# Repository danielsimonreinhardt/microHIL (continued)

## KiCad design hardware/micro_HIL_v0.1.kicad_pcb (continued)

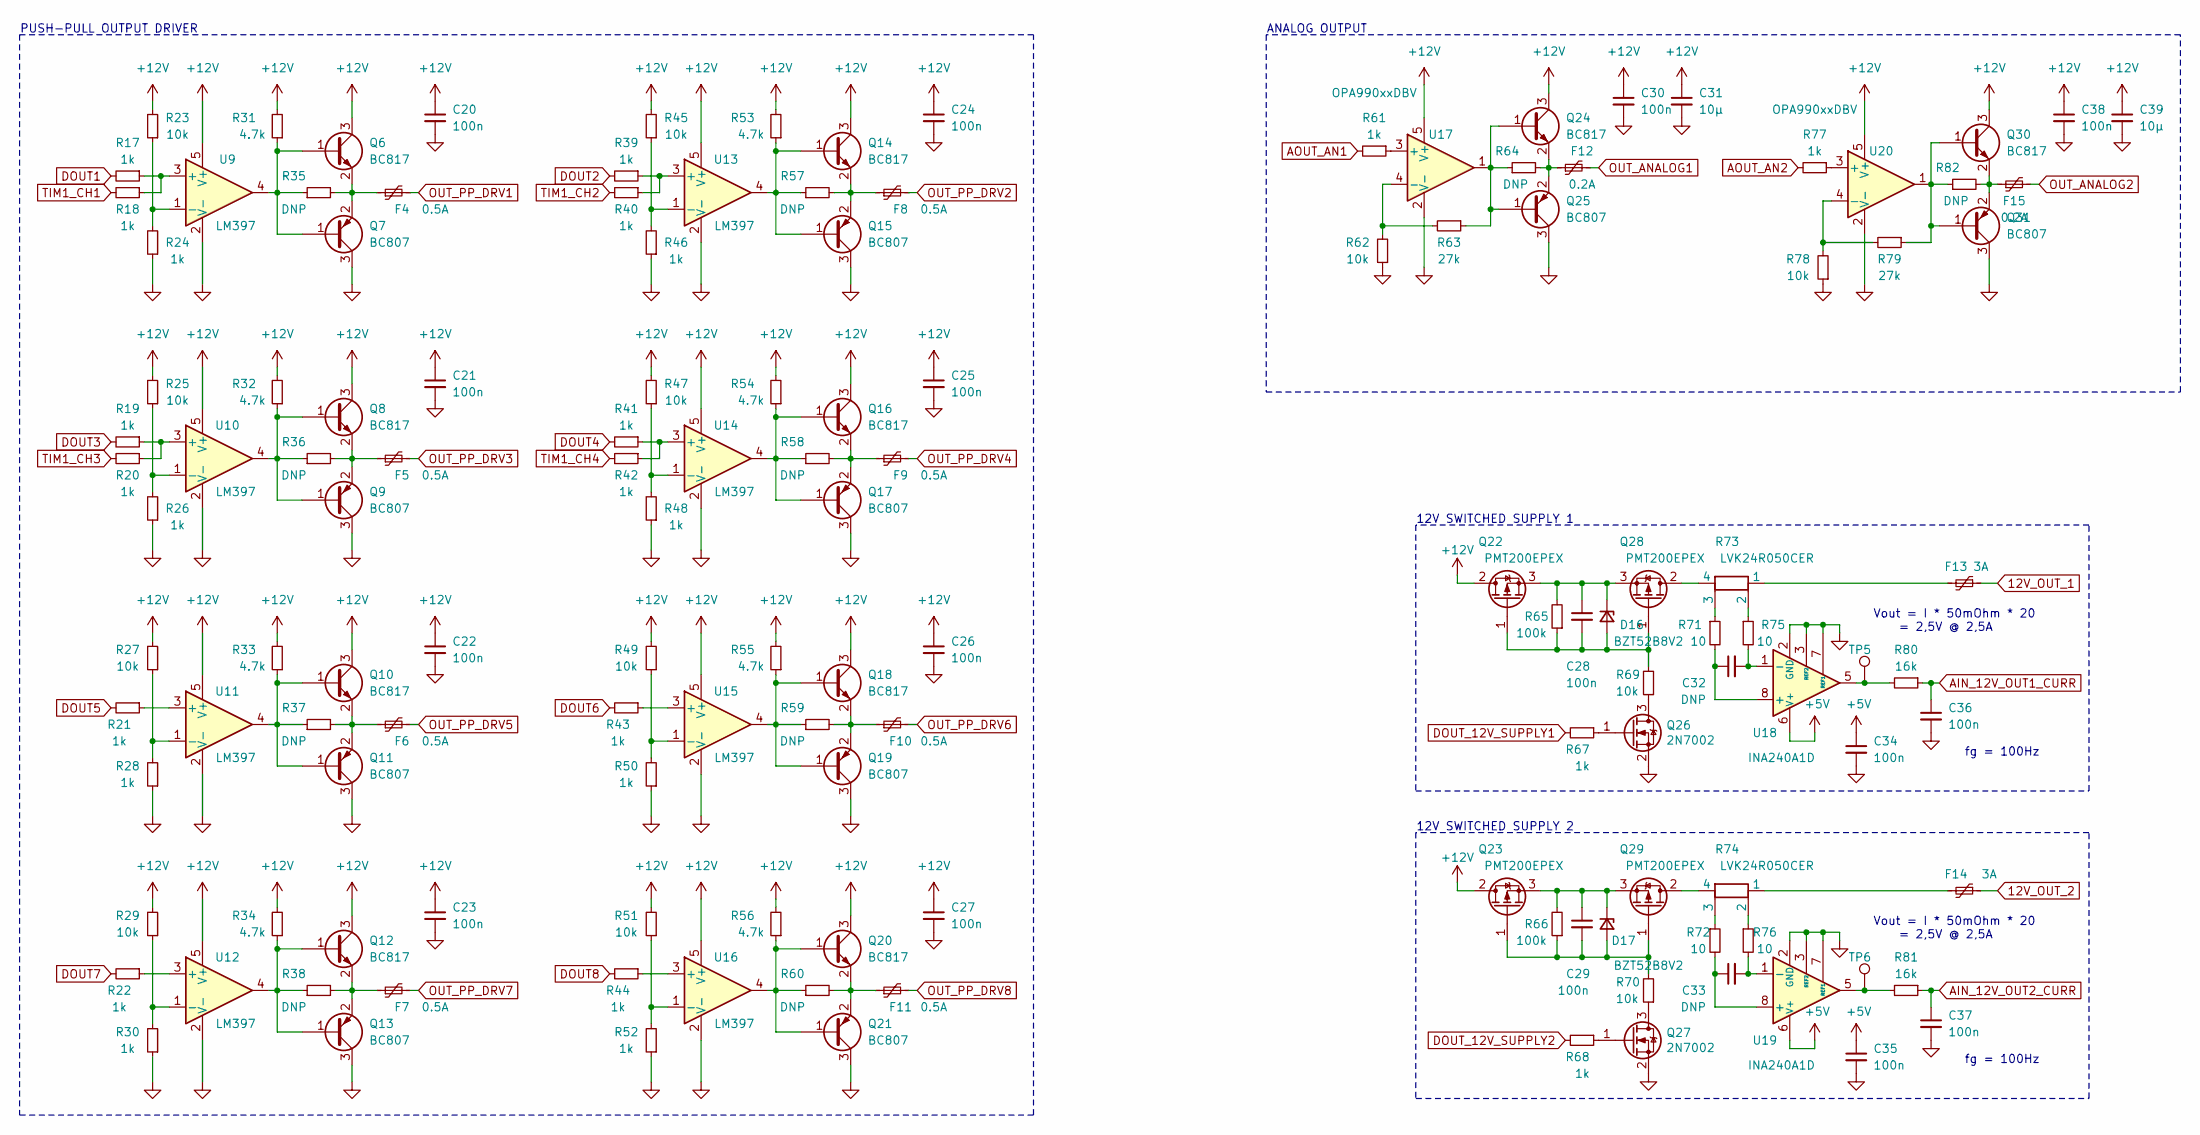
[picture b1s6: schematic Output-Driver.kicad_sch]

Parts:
C20, C21, C22, C23, C24, C25, C26, C27, C28, C29, C30, C34, C35, C36, C37, C38: 100n; C_0603_1608Metric
C31, C39: 10µ; C_0805_2012Metric
C32, C33: DNP; C_0603_1608Metric
D16, D17: BZT52B8V2; D_SOD-123
F4, F5, F6, F7, F8, F9, F10, F11: 0.5A; Fuse_1210_3225Metric
F12, F15: 0.2A; Fuse_1210_3225Metric
F13, F14: 3A; Fuse_1812_4532Metric
Q6, Q8, Q10, Q12, Q14, Q16, Q18, Q20, Q24, Q30: BC817; SOT-23
Q7, Q9, Q11, Q13, Q15, Q17, Q19, Q21, Q25, Q31: BC807; SOT-23
Q22, Q23, Q28, Q29: PMT200EPEX; SOT-223-3_TabPin2
Q26, Q27: 2N7002; SOT-23
R17, R18, R19, R20, R21, R22, R24, R26, R28, R30, R39, R40, R41, R42, R43, R44, R46, R48, R50, R52, R61, R67, R68, R77: 1k; R_0603_1608Metric
R23, R25, R27, R29, R45, R47, R49, R51, R62, R69, R70, R78: 10k; R_0603_1608Metric
R31, R32, R33, R34, R53, R54, R55, R56: 4.7k; R_0603_1608Metric
R35, R36, R37, R38, R57, R58, R59, R60, R64, R82: DNP; R_0603_1608Metric
R63, R79: 27k; R_0603_1608Metric
R65, R66: 100k; R_0603_1608Metric
R71, R72, R75, R76: 10; R_0603_1608Metric
R73, R74: LVK24R050CER; R_Shunt_Ohmite_LVK24
R80, R81: 16k; R_0603_1608Metric
TP5, TP6: TestPoint; TestPoint_Pad_D1.0mm
U9, U10, U11, U12, U13, U14, U15, U16: LM397; SOT-23-5
U17, U20: OPA990xxDBV; SOT-23-5
U18, U19: INA240A1D; SOIC-8_3.9x4.9mm_P1.27mm

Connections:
12V_OUT_1: F13.1; also elsewhere on the board
12V_OUT_2: F14.1; also elsewhere on the board
+5V: C34.1, C35.1, U18.6 (V+), U19.6 (V+); also elsewhere on the board
+12V: C20.1, C21.1, C22.1, C23.1, C24.1, C25.1, C26.1, C27.1, C30.1, C31.1, C38.1, C39.1, Q6.3 (C), Q8.3 (C), Q10.3 (C), Q12.3 (C), Q14.3 (C), Q16.3 (C), Q18.3 (C), Q20.3 (C), Q22.2 (D), Q23.2 (D), Q24.3 (C), Q30.3 (C), R23.2, R25.2, R27.2, R29.2, R31.2, R32.2, R33.2, R34.2, R45.2, R47.2, R49.2, R51.2, R53.2, R54.2, R55.2, R56.2, U9.5 (V+), U10.5 (V+), U11.5 (V+), U12.5 (V+), U13.5 (V+), U14.5 (V+), U15.5 (V+), U16.5 (V+), U17.5 (V+), U20.5 (V+); also elsewhere on the board
AIN_12V_OUT1_CURR: C36.1, R80.1; also elsewhere on the board
AIN_12V_OUT2_CURR: C37.1, R81.1; also elsewhere on the board
AOUT_AN1: R61.2; also elsewhere on the board
AOUT_AN2: R77.2; also elsewhere on the board
DOUT1: R17.2; also elsewhere on the board
DOUT2: R39.2; also elsewhere on the board
DOUT3: R19.2; also elsewhere on the board
DOUT4: R41.2; also elsewhere on the board
DOUT5: R21.2; also elsewhere on the board
DOUT6: R43.2; also elsewhere on the board
DOUT7: R22.2; also elsewhere on the board
DOUT8: R44.2; also elsewhere on the board
DOUT_12V_SUPPLY1: R67.2; also elsewhere on the board
DOUT_12V_SUPPLY2: R68.2; also elsewhere on the board
GND: C20.2, C21.2, C22.2, C23.2, C24.2, C25.2, C26.2, C27.2, C30.2, C31.2, C34.2, C35.2, C36.2, C37.2, C38.2, C39.2, Q7.3 (C), Q9.3 (C), Q11.3 (C), Q13.3 (C), Q15.3 (C), Q17.3 (C), Q19.3 (C), Q21.3 (C), Q25.3 (C), Q26.2 (S), Q27.2 (S), Q31.3 (C), R24.1, R26.1, R28.1, R30.1, R46.1, R48.1, R50.1, R52.1, R62.1, R78.1, U9.2 (V-), U10.2 (V-), U11.2 (V-), U12.2 (V-), U13.2 (V-), U14.2 (V-), U15.2 (V-), U16.2 (V-), U17.2 (V-), U18.2 (GND), U18.3 (REF2), U18.4 (GND), U18.7 (REF1), U19.2 (GND), U19.3 (REF2), U19.4 (GND), U19.7 (REF1), U20.2 (V-); also elsewhere on the board
unnamed: C28.1, D16.1 (K), Q22.3 (S), Q28.3 (S), R65.2
unnamed: C28.2, D16.2 (A), Q22.1 (G), Q28.1 (G), R65.1, R69.2
unnamed: C29.1, D17.1 (K), Q23.3 (S), Q29.3 (S), R66.2
unnamed: C29.2, D17.2 (A), Q23.1 (G), Q29.1 (G), R66.1, R70.2
unnamed: C32.1, R71.2, U18.8 (+)
unnamed: C32.2, R75.2, U18.1 (-)
unnamed: C33.1, R72.2, U19.8 (+)
unnamed: C33.2, R76.2, U19.1 (-)
unnamed: F4.1, Q6.2 (E), Q7.2 (E), R35.2
unnamed: F5.1, Q8.2 (E), Q9.2 (E), R36.2
unnamed: F6.1, Q10.2 (E), Q11.2 (E), R37.2
unnamed: F7.1, Q12.2 (E), Q13.2 (E), R38.2
unnamed: F8.1, Q14.2 (E), Q15.2 (E), R57.2
unnamed: F9.1, Q16.2 (E), Q17.2 (E), R58.2
unnamed: F10.1, Q18.2 (E), Q19.2 (E), R59.2
unnamed: F11.1, Q20.2 (E), Q21.2 (E), R60.2
unnamed: F12.1, Q24.2 (E), Q25.2 (E), R64.2
unnamed: F13.2, R73.1
unnamed: F14.2, R74.1
unnamed: F15.1, Q30.2 (E), Q31.2 (E), R82.2
unnamed: Q6.1 (B), Q7.1 (B), R31.1, R35.1, U9.4
unnamed: Q8.1 (B), Q9.1 (B), R32.1, R36.1, U10.4
unnamed: Q10.1 (B), Q11.1 (B), R33.1, R37.1, U11.4
unnamed: Q12.1 (B), Q13.1 (B), R34.1, R38.1, U12.4
unnamed: Q14.1 (B), Q15.1 (B), R53.1, R57.1, U13.4
unnamed: Q16.1 (B), Q17.1 (B), R54.1, R58.1, U14.4
unnamed: Q18.1 (B), Q19.1 (B), R55.1, R59.1, U15.4
unnamed: Q20.1 (B), Q21.1 (B), R56.1, R60.1, U16.4
unnamed: Q24.1 (B), Q25.1 (B), R63.1, R64.1, U17.1
unnamed: Q26.1 (G), R67.1
unnamed: Q26.3 (D), R69.1
unnamed: Q27.1 (G), R68.1
unnamed: Q27.3 (D), R70.1
unnamed: Q28.2 (D), R73.4
unnamed: Q29.2 (D), R74.4
unnamed: Q30.1 (B), Q31.1 (B), R79.1, R82.1, U20.1
unnamed: R17.1, R18.1, U9.3 (+)
unnamed: R19.1, R20.1, U10.3 (+)
unnamed: R21.1, U11.3 (+)
unnamed: R22.1, U12.3 (+)
unnamed: R23.1, R24.2, U9.1 (-)
unnamed: R25.1, R26.2, U10.1 (-)
unnamed: R27.1, R28.2, U11.1 (-)
unnamed: R29.1, R30.2, U12.1 (-)
unnamed: R39.1, R40.1, U13.3 (+)
unnamed: R41.1, R42.1, U14.3 (+)
unnamed: R43.1, U15.3 (+)
unnamed: R44.1, U16.3 (+)
unnamed: R45.1, R46.2, U13.1 (-)
unnamed: R47.1, R48.2, U14.1 (-)
unnamed: R49.1, R50.2, U15.1 (-)
unnamed: R51.1, R52.2, U16.1 (-)
unnamed: R61.1, U17.3 (+)
unnamed: R62.2, R63.2, U17.4 (-)
unnamed: R71.1, R73.3
unnamed: R72.1, R74.3
unnamed: R73.2, R75.1
unnamed: R74.2, R76.1
unnamed: R77.1, U20.3 (+)
unnamed: R78.2, R79.2, U20.4 (-)
unnamed: R80.2, TP5.1, U18.5
unnamed: R81.2, TP6.1, U19.5
OUT_ANALOG1: F12.2; also elsewhere on the board
OUT_ANALOG2: F15.2; also elsewhere on the board
OUT_PP_DRV1: F4.2; also elsewhere on the board
OUT_PP_DRV2: F8.2; also elsewhere on the board
OUT_PP_DRV3: F5.2; also elsewhere on the board
OUT_PP_DRV4: F9.2; also elsewhere on the board
OUT_PP_DRV5: F6.2; also elsewhere on the board
OUT_PP_DRV6: F10.2; also elsewhere on the board
OUT_PP_DRV7: F7.2; also elsewhere on the board
OUT_PP_DRV8: F11.2; also elsewhere on the board
TIM1_CH1: R18.2; also elsewhere on the board
TIM1_CH2: R40.2; also elsewhere on the board
TIM1_CH3: R20.2; also elsewhere on the board
TIM1_CH4: R42.2; also elsewhere on the board

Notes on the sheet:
Vout = I * 50mOhm * 20 = 2,5V @ 2,5A
12V SWITCHED SUPPLY 2
fg = 100Hz
ANALOG OUTPUT
12V SWITCHED SUPPLY 1
PUSH-PULL OUTPUT DRIVER

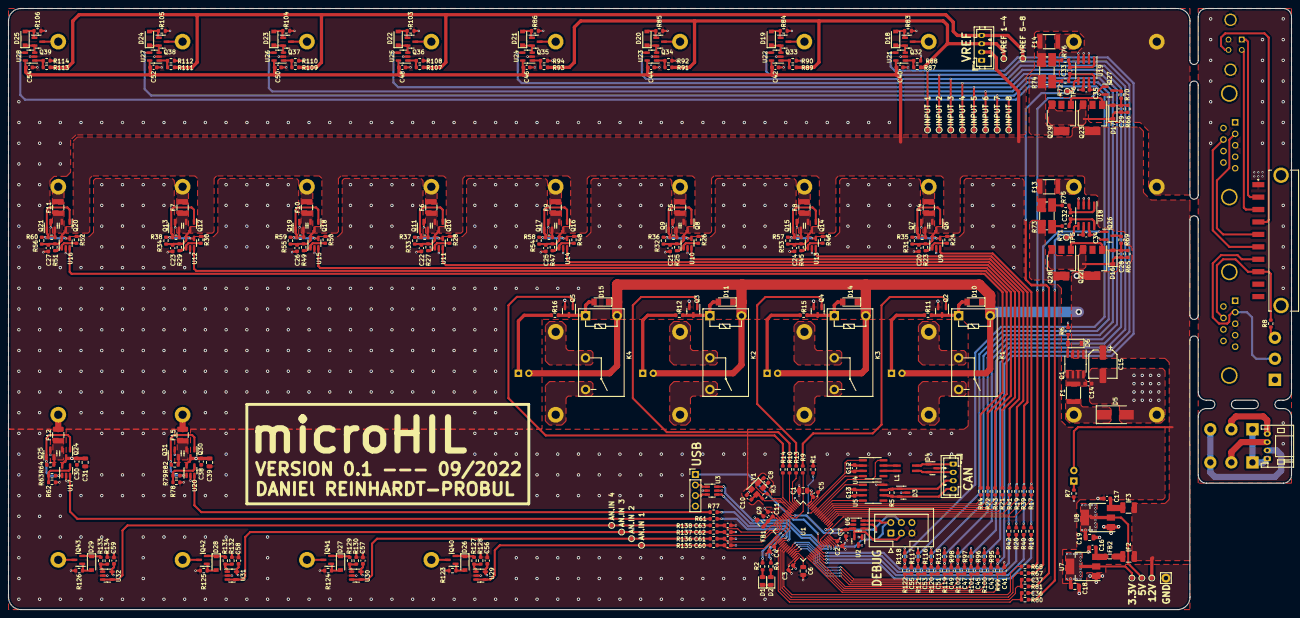
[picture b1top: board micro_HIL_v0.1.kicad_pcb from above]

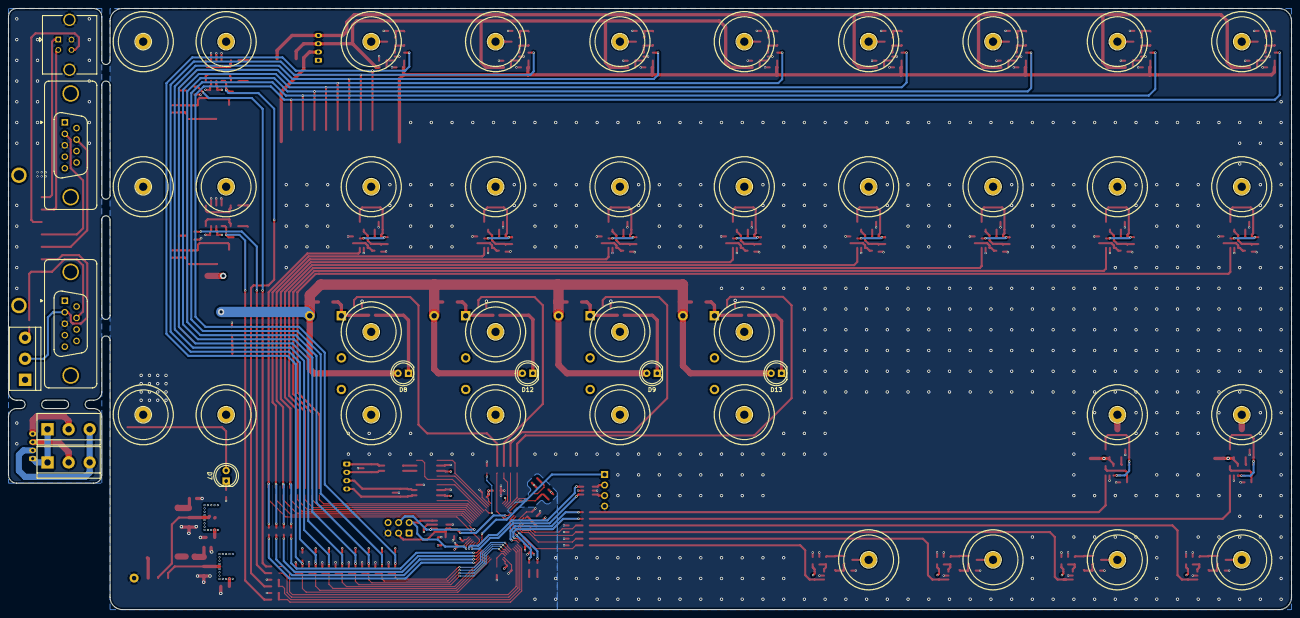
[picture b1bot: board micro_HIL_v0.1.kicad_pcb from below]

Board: 4 copper layers, 309.5 x 145.0 mm, 396 parts (47 on the bottom side), 242 nets.

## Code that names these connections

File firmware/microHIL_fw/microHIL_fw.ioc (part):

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Mcu.Name=STM32F446R(C-E)Tx
Mcu.Package=LQFP64
Mcu.UserName=STM32F446RETx
PA0-WKUP.GPIOParameters=GPIO_Label
PA0-WKUP.GPIO_Label=AIN_AN2
PA0-WKUP.Signal=ADCx_IN0
PA1.GPIOParameters=GPIO_Label
PA1.GPIO_Label=AIN_AN3
PA1.Signal=ADCx_IN1
PA10.GPIOParameters=GPIO_Label
PA10.GPIO_Label=DOUT_OUT1
PA10.Signal=GPIO_Output
PA11.Mode=Device_Only
PA11.Signal=USB_OTG_FS_DM
PA12.Mode=Device_Only
PA12.Signal=USB_OTG_FS_DP
PA13.Mode=Serial_Wire
PA13.Signal=SYS_JTMS-SWDIO
PA14.Mode=Serial_Wire
PA14.Signal=SYS_JTCK-SWCLK
PA15.GPIOParameters=GPIO_Label
PA15.GPIO_Label=DOUT_OUT2
PA15.Signal=GPIO_Output
PA2.GPIOParameters=GPIO_Label
PA2.GPIO_Label=AIN_AN4
PA2.Signal=ADCx_IN2
PA3.GPIOParameters=GPIO_Label
PA3.GPIO_Label=AIN_AN1
PA3.Signal=ADCx_IN3
PA4.GPIOParameters=GPIO_Label
PA4.GPIO_Label=AOUT_AN2
PA4.Signal=COMP_DAC1_group
PA5.GPIOParameters=GPIO_Label
PA5.GPIO_Label=AOUT_AN1
PA5.Signal=COMP_DAC2_group
PA6.GPIOParameters=GPIO_Label
PA6.GPIO_Label=AIN_12VOUT1_CURRSENSE
PA6.Signal=ADCx_IN6
PA7.GPIOParameters=GPIO_Label
PA7.GPIO_Label=AIN_12VOUT2_CURRSENSE
PA7.Signal=ADCx_IN7
PB0.GPIOParameters=GPIO_Label
PB0.GPIO_Label=DIN_IN8
PB0.Signal=GPIO_Input
PB1.GPIOParameters=GPIO_Label
PB1.GPIO_Label=DIN_IN7
PB1.Signal=GPIO_Input
PB10.GPIOParameters=GPIO_Label
PB10.GPIO_Label=DIN_IN5
PB10.Signal=GPIO_Input
PB12.GPIOParameters=GPIO_Label
PB12.GPIO_Label=DIN_IN1
PB12.Signal=GPIO_Input
PB13.GPIOParameters=GPIO_Label
PB13.GPIO_Label=DIN_IN2
PB13.Signal=GPIO_Input
PB14.GPIOParameters=GPIO_Label
PB14.GPIO_Label=DIN_IN3
PB14.Signal=GPIO_Input
PB15.GPIOParameters=GPIO_Label
PB15.GPIO_Label=DIN_IN4
PB15.Signal=GPIO_Input
PB2.GPIOParameters=GPIO_Label
PB2.GPIO_Label=DIN_IN6
PB2.Signal=GPIO_Input
PB3.GPIOParameters=GPIO_Label
PB3.GPIO_Label=DOUT_OUT7
PB3.Signal=GPIO_Output
PB4.GPIOParameters=GPIO_Label
PB4.GPIO_Label=DOUT_OUT8
PB4.Signal=GPIO_Output
PB5.Mode=CAN_Activate
PB5.Signal=CAN2_RX
PB6.Mode=CAN_Activate
PB6.Signal=CAN2_TX
PB7.GPIOParameters=GPIO_Label
PB7.GPIO_Label=CAN1_SILENT
PB7.Signal=GPIO_Output
PB8.Mode=CAN_Activate
PB8.Signal=CAN1_RX
PB9.Mode=CAN_Activate
PB9.Signal=CAN1_TX
PC0.GPIOParameters=GPIO_Label
PC0.GPIO_Label=DOUT_RELAY1
PC0.Signal=GPIO_Output
PC1.GPIOParameters=GPIO_Label
PC1.GPIO_Label=DEBUG_LED_1
PC1.Signal=GPIO_Output
PC10.GPIOParameters=GPIO_Label
PC10.GPIO_Label=DOUT_OUT3
PC10.Signal=GPIO_Output
PC11.GPIOParameters=GPIO_Label
PC11.GPIO_Label=DOUT_OUT4
PC11.Signal=GPIO_Output
PC12.GPIOParameters=GPIO_Label
PC12.GPIO_Label=DOUT_OUT5
PC12.Signal=GPIO_Output
PC13.GPIOParameters=GPIO_Label
PC13.GPIO_Label=DOUT_RELAY2
PC13.Signal=GPIO_Output
PC14-OSC32_IN.GPIOParameters=GPIO_Label
PC14-OSC32_IN.GPIO_Label=DOUT_RELAY3
PC14-OSC32_IN.Signal=GPIO_Output
PC15-OSC32_OUT.GPIOParameters=GPIO_Label
PC15-OSC32_OUT.GPIO_Label=DOUT_RELAY4
PC15-OSC32_OUT.Signal=GPIO_Output
PC2.GPIOParameters=GPIO_Label
PC2.GPIO_Label=DEBUG_LED_2
PC2.Signal=GPIO_Output
PC4.GPIOParameters=GPIO_Label
PC4.GPIO_Label=DOUT_12VOUT1
PC4.Signal=GPIO_Output
PC5.GPIOParameters=GPIO_Label
PC5.GPIO_Label=DOUT_12VOUT2
PC5.Signal=GPIO_Output
PC6.Signal=S_TIM3_CH1
PC7.Signal=S_TIM3_CH2
PC8.Signal=S_TIM3_CH3
PC9.Signal=S_TIM3_CH4
PD2.GPIOParameters=GPIO_Label
PD2.GPIO_Label=DOUT_OUT6
PD2.Signal=GPIO_Output
PH0-OSC_IN.Mode=HSE-External-Oscillator
PH0-OSC_IN.Signal=RCC_OSC_IN
PH1-OSC_OUT.Mode=HSE-External-Oscillator
PH1-OSC_OUT.Signal=RCC_OSC_OUT
RCC.HSE_VALUE=8000000
RCC.SYSCLKFreq_VALUE=72000000
RCC.SYSCLKSource=RCC_SYSCLKSOURCE_PLLCLK
board=custom
